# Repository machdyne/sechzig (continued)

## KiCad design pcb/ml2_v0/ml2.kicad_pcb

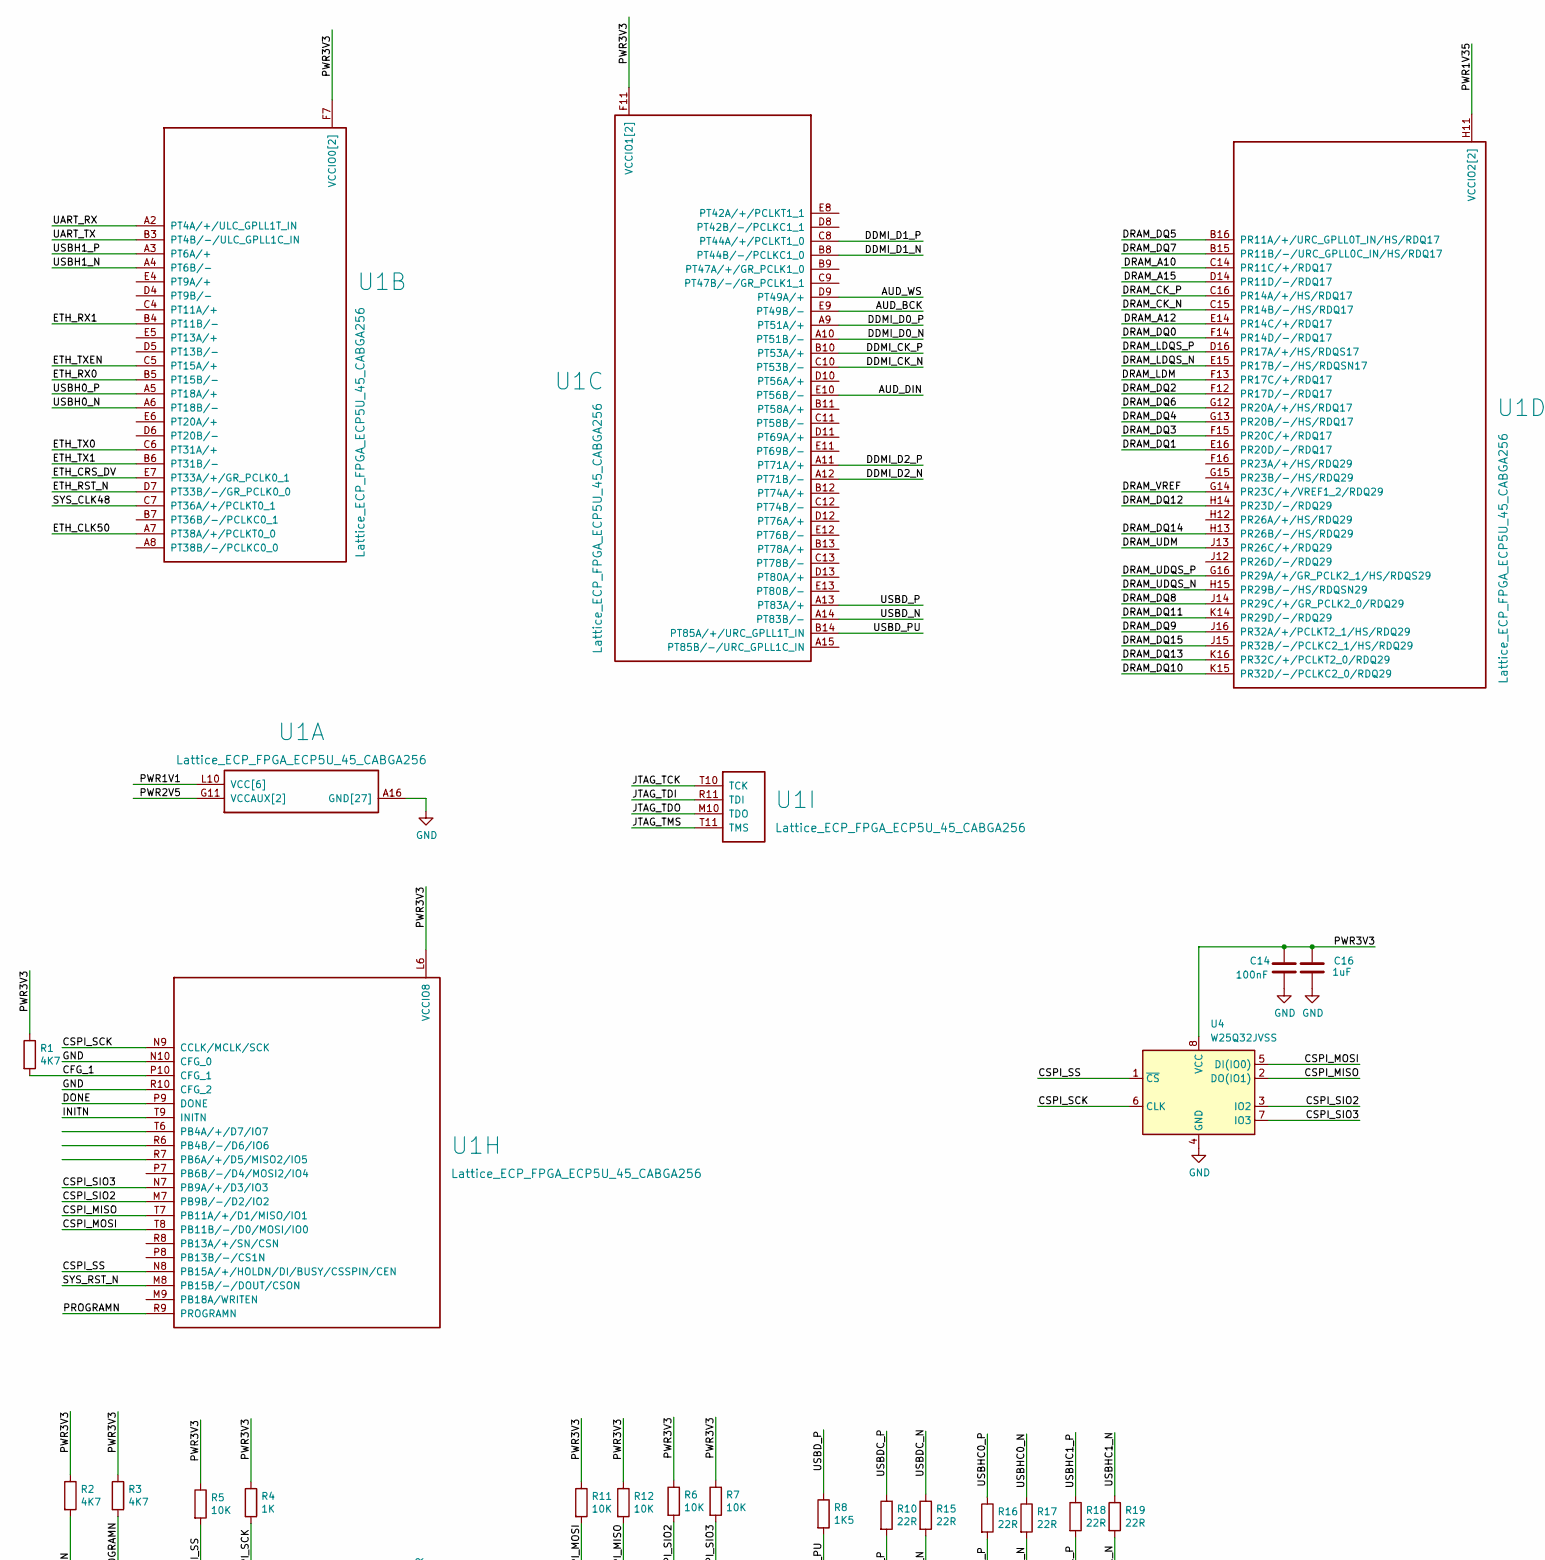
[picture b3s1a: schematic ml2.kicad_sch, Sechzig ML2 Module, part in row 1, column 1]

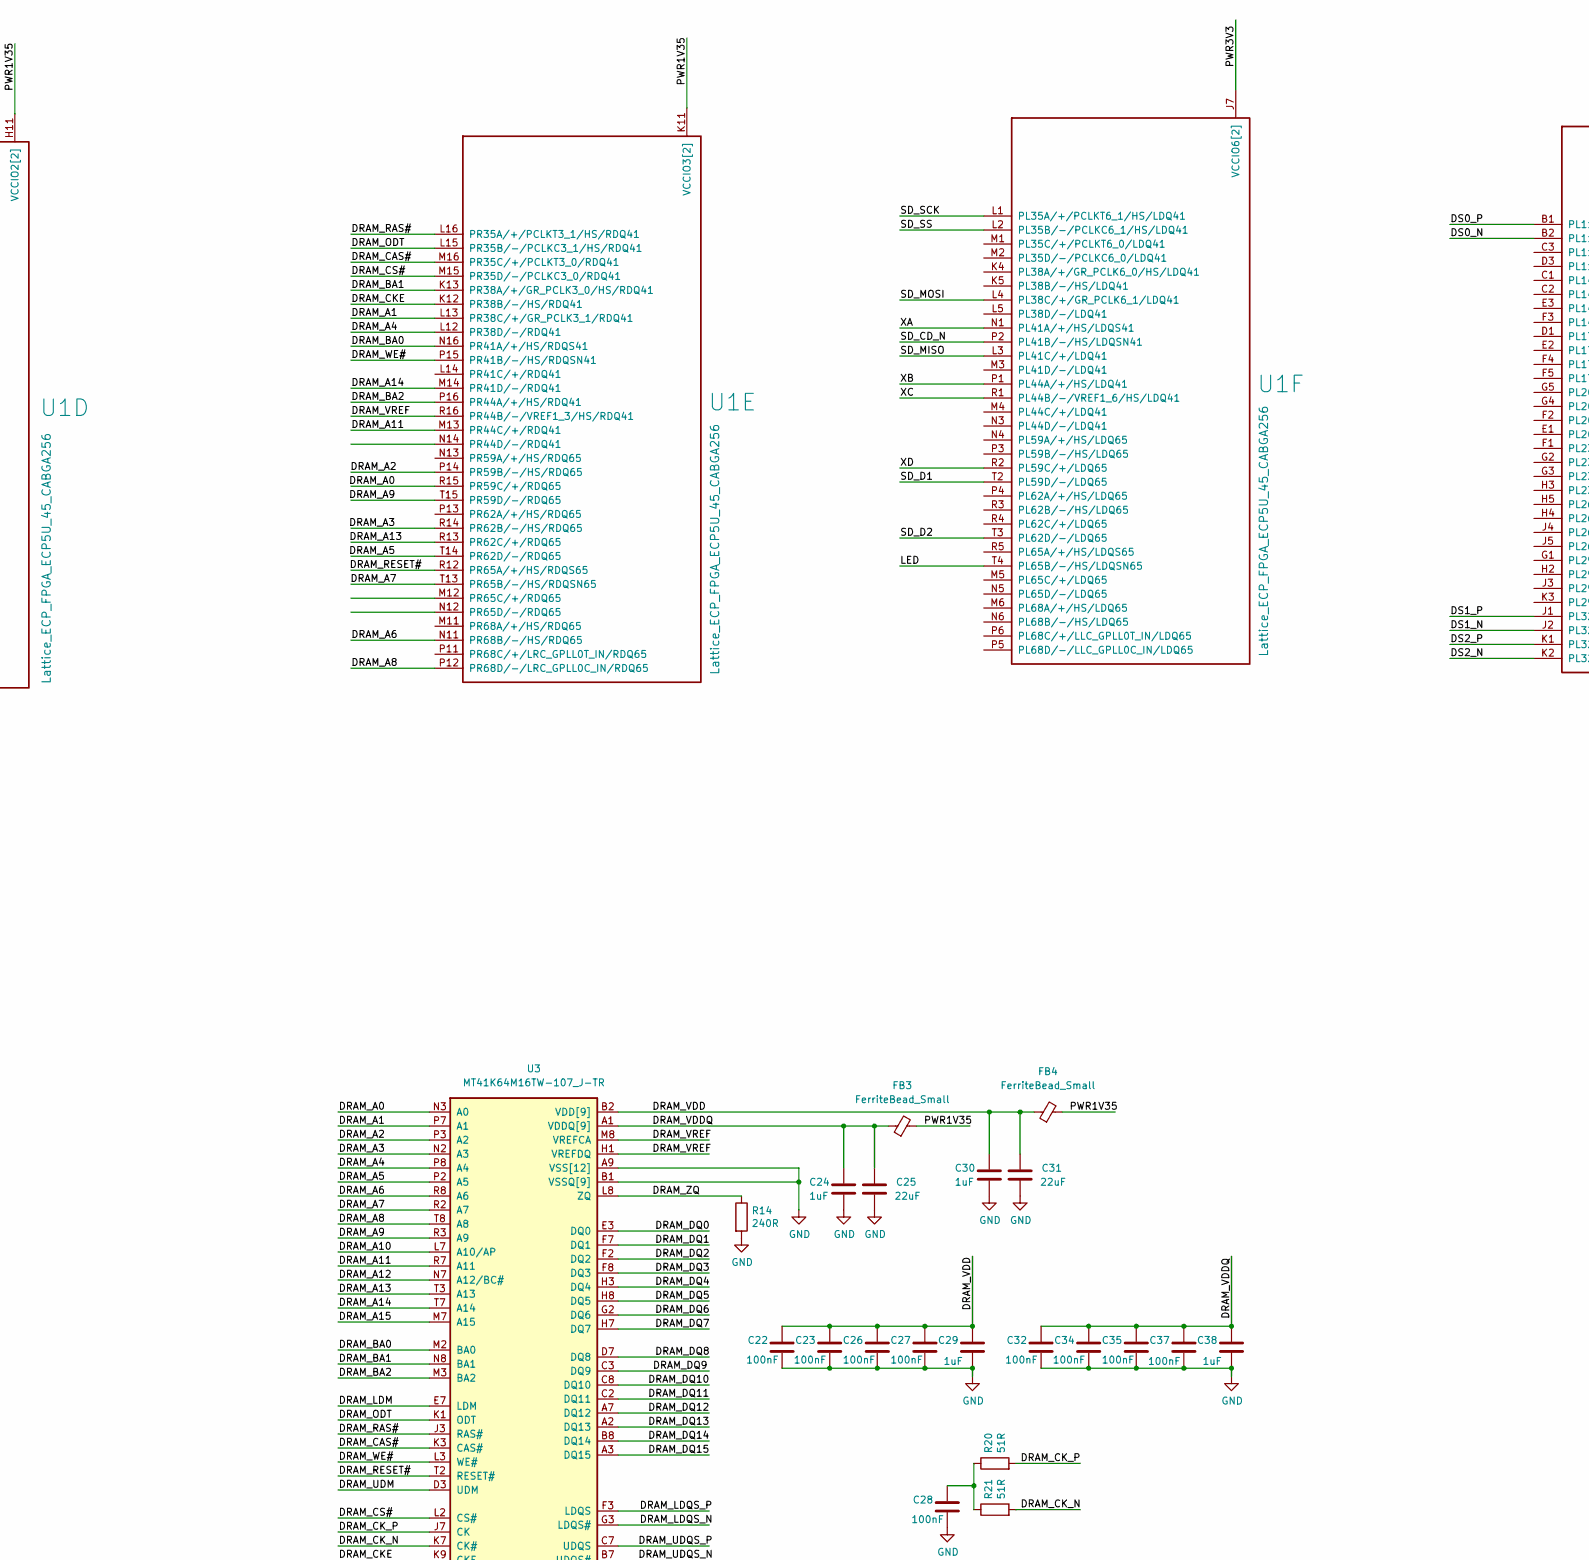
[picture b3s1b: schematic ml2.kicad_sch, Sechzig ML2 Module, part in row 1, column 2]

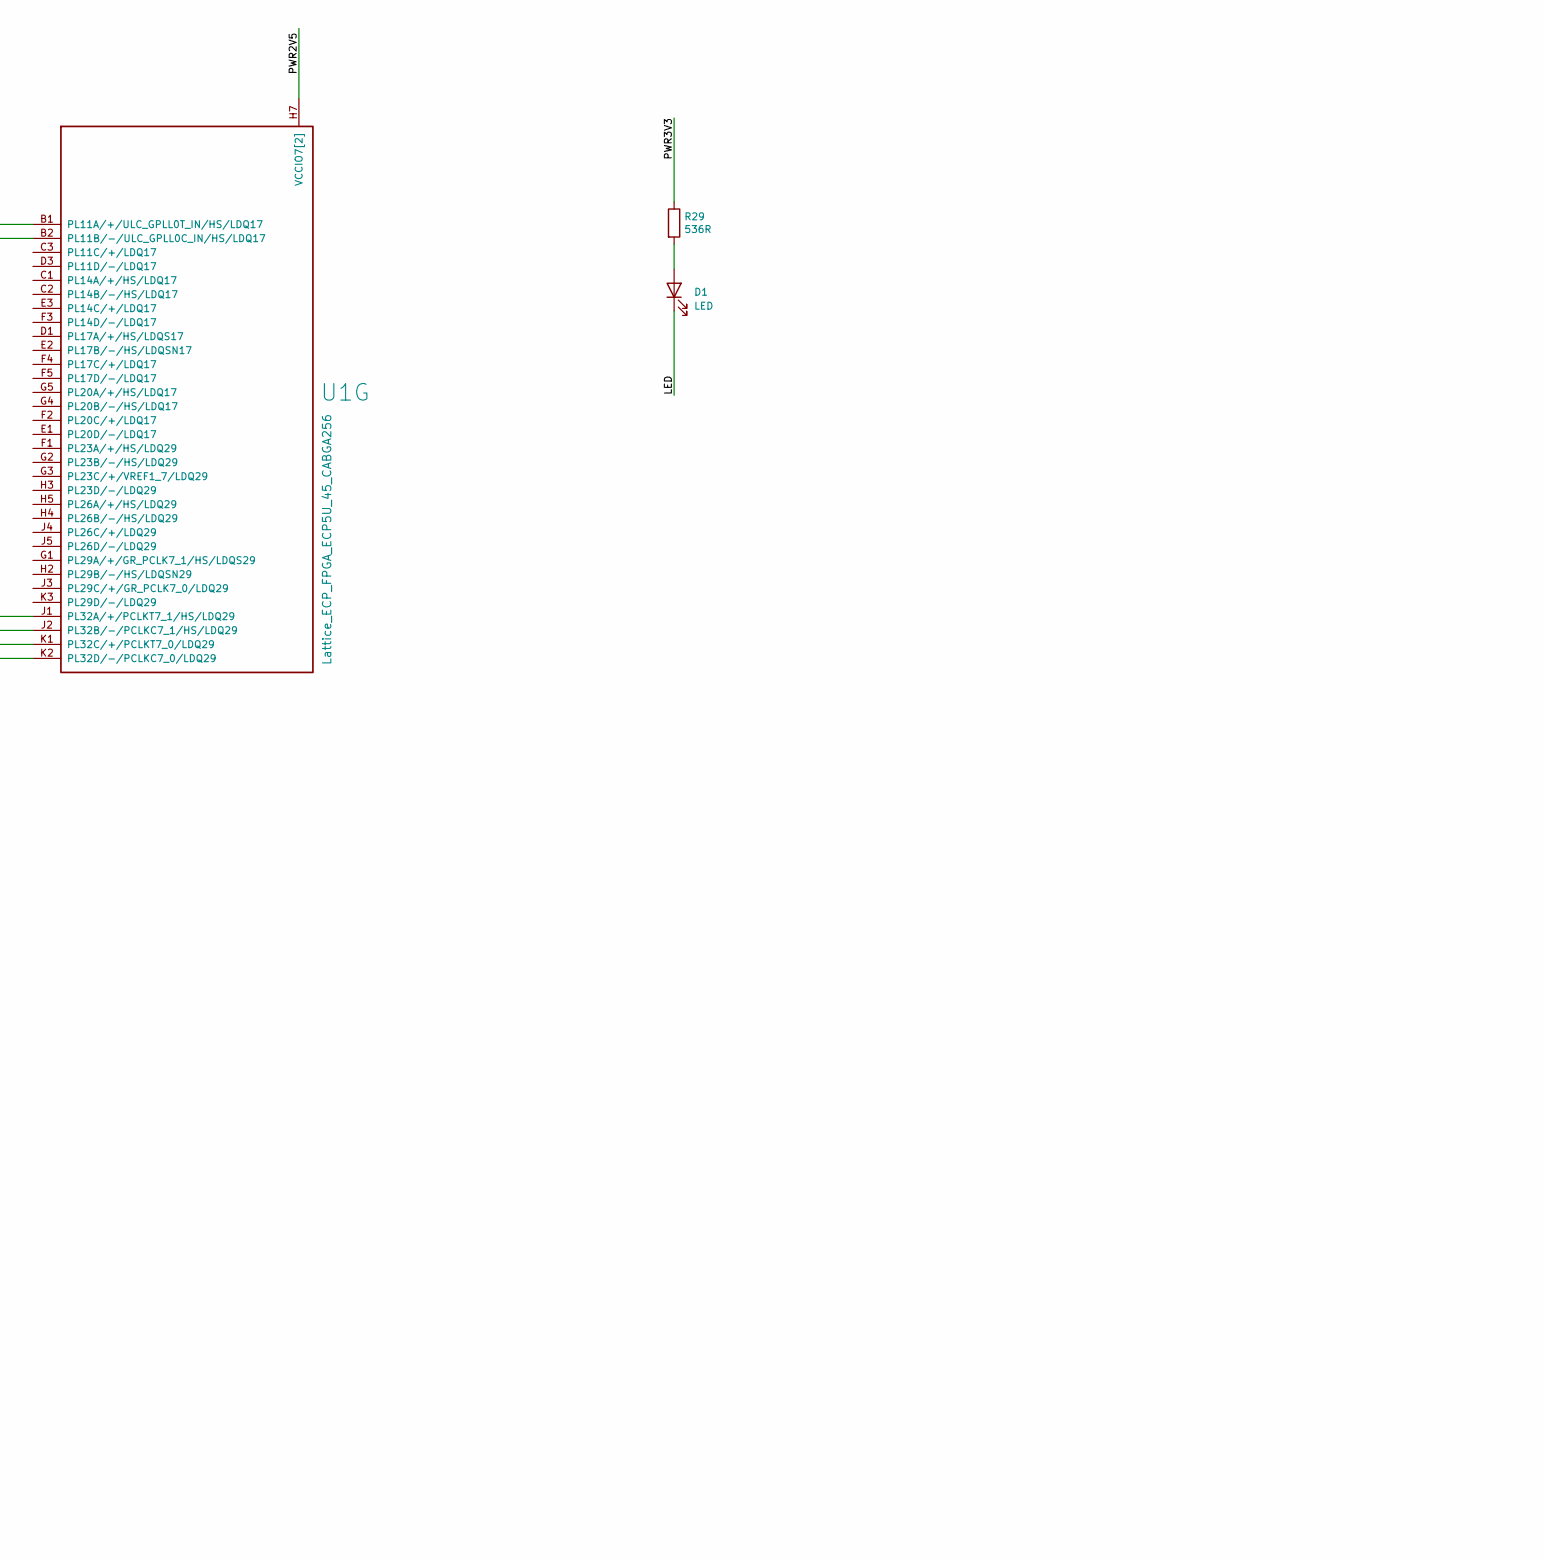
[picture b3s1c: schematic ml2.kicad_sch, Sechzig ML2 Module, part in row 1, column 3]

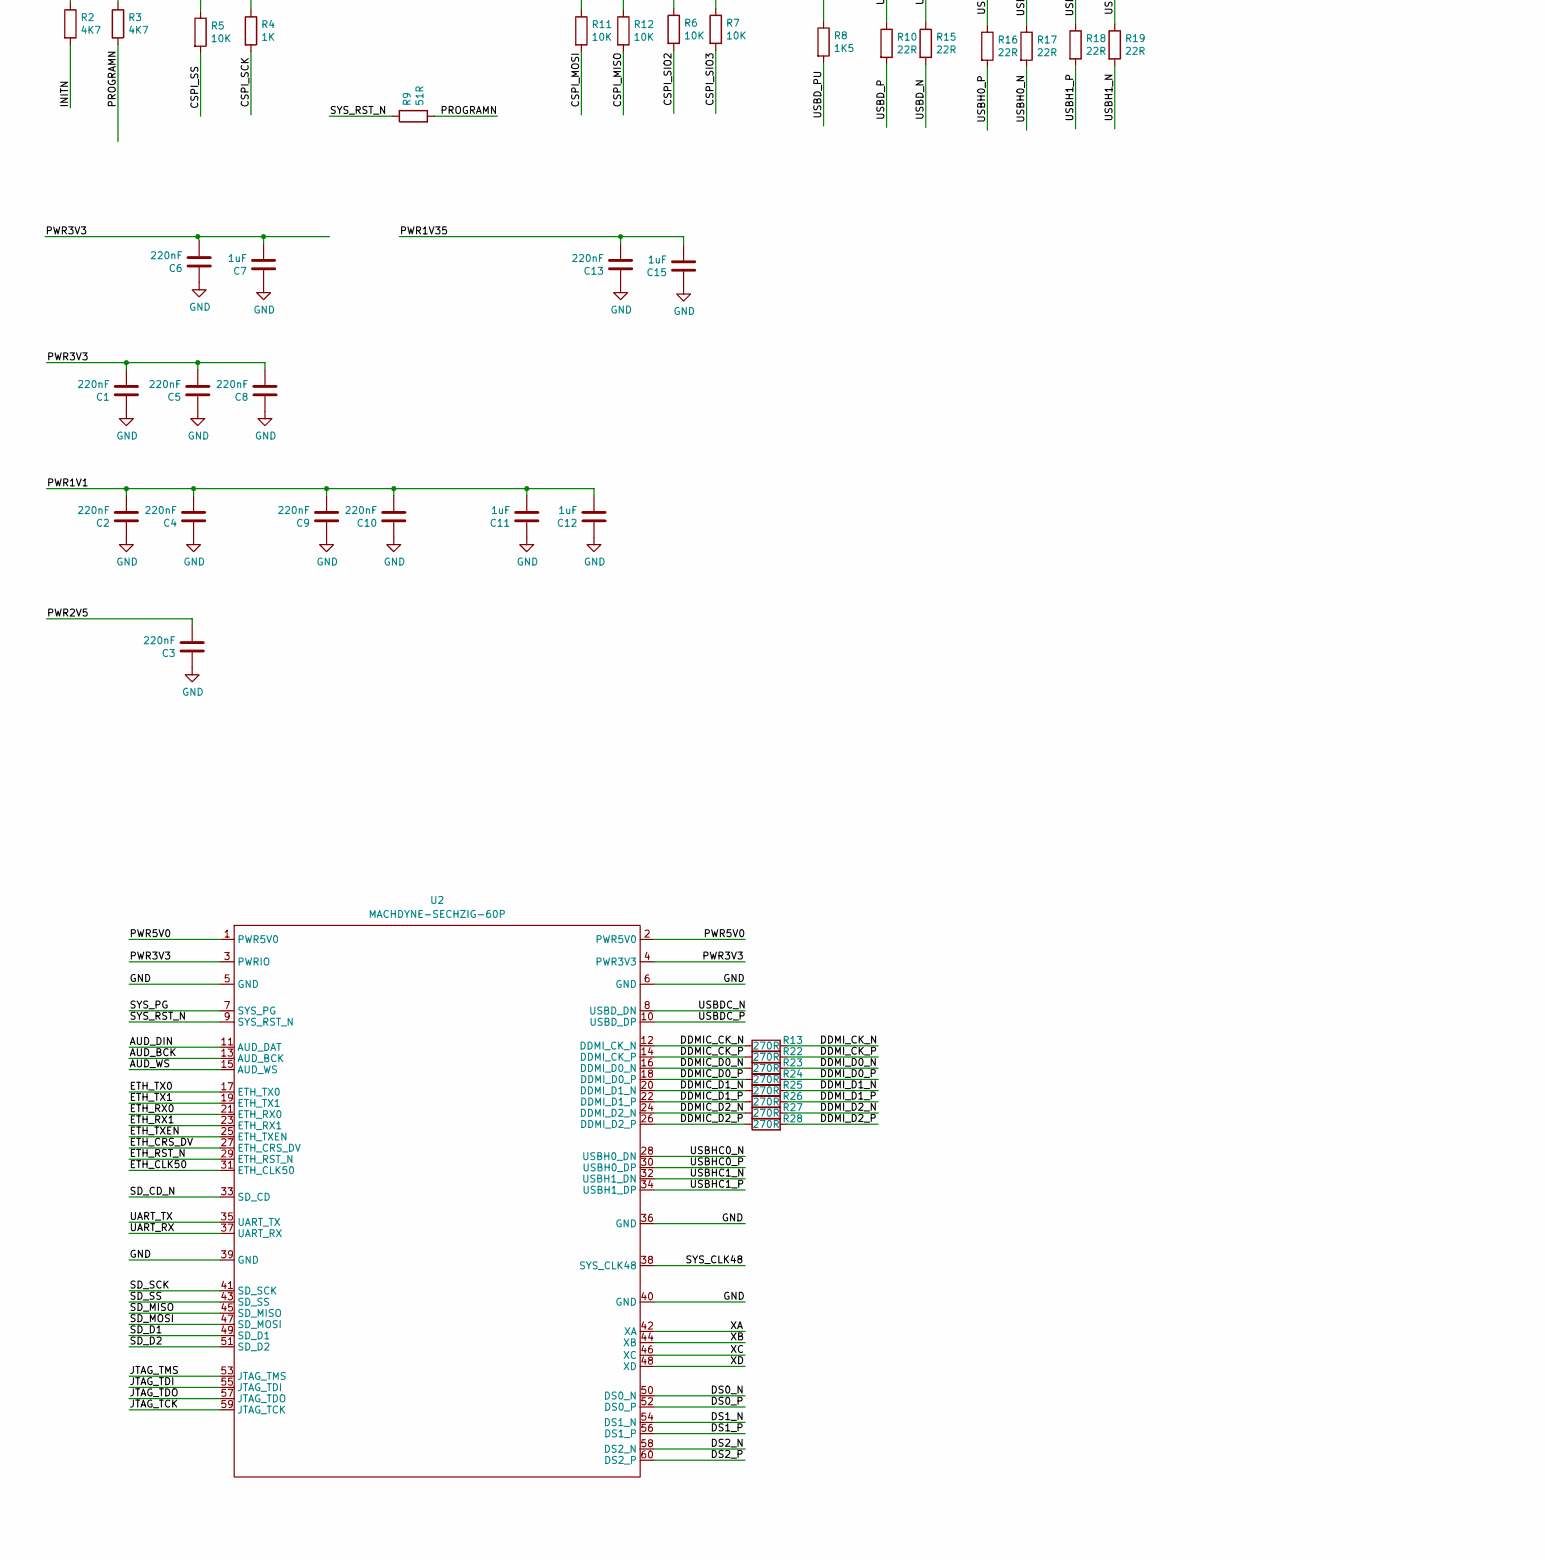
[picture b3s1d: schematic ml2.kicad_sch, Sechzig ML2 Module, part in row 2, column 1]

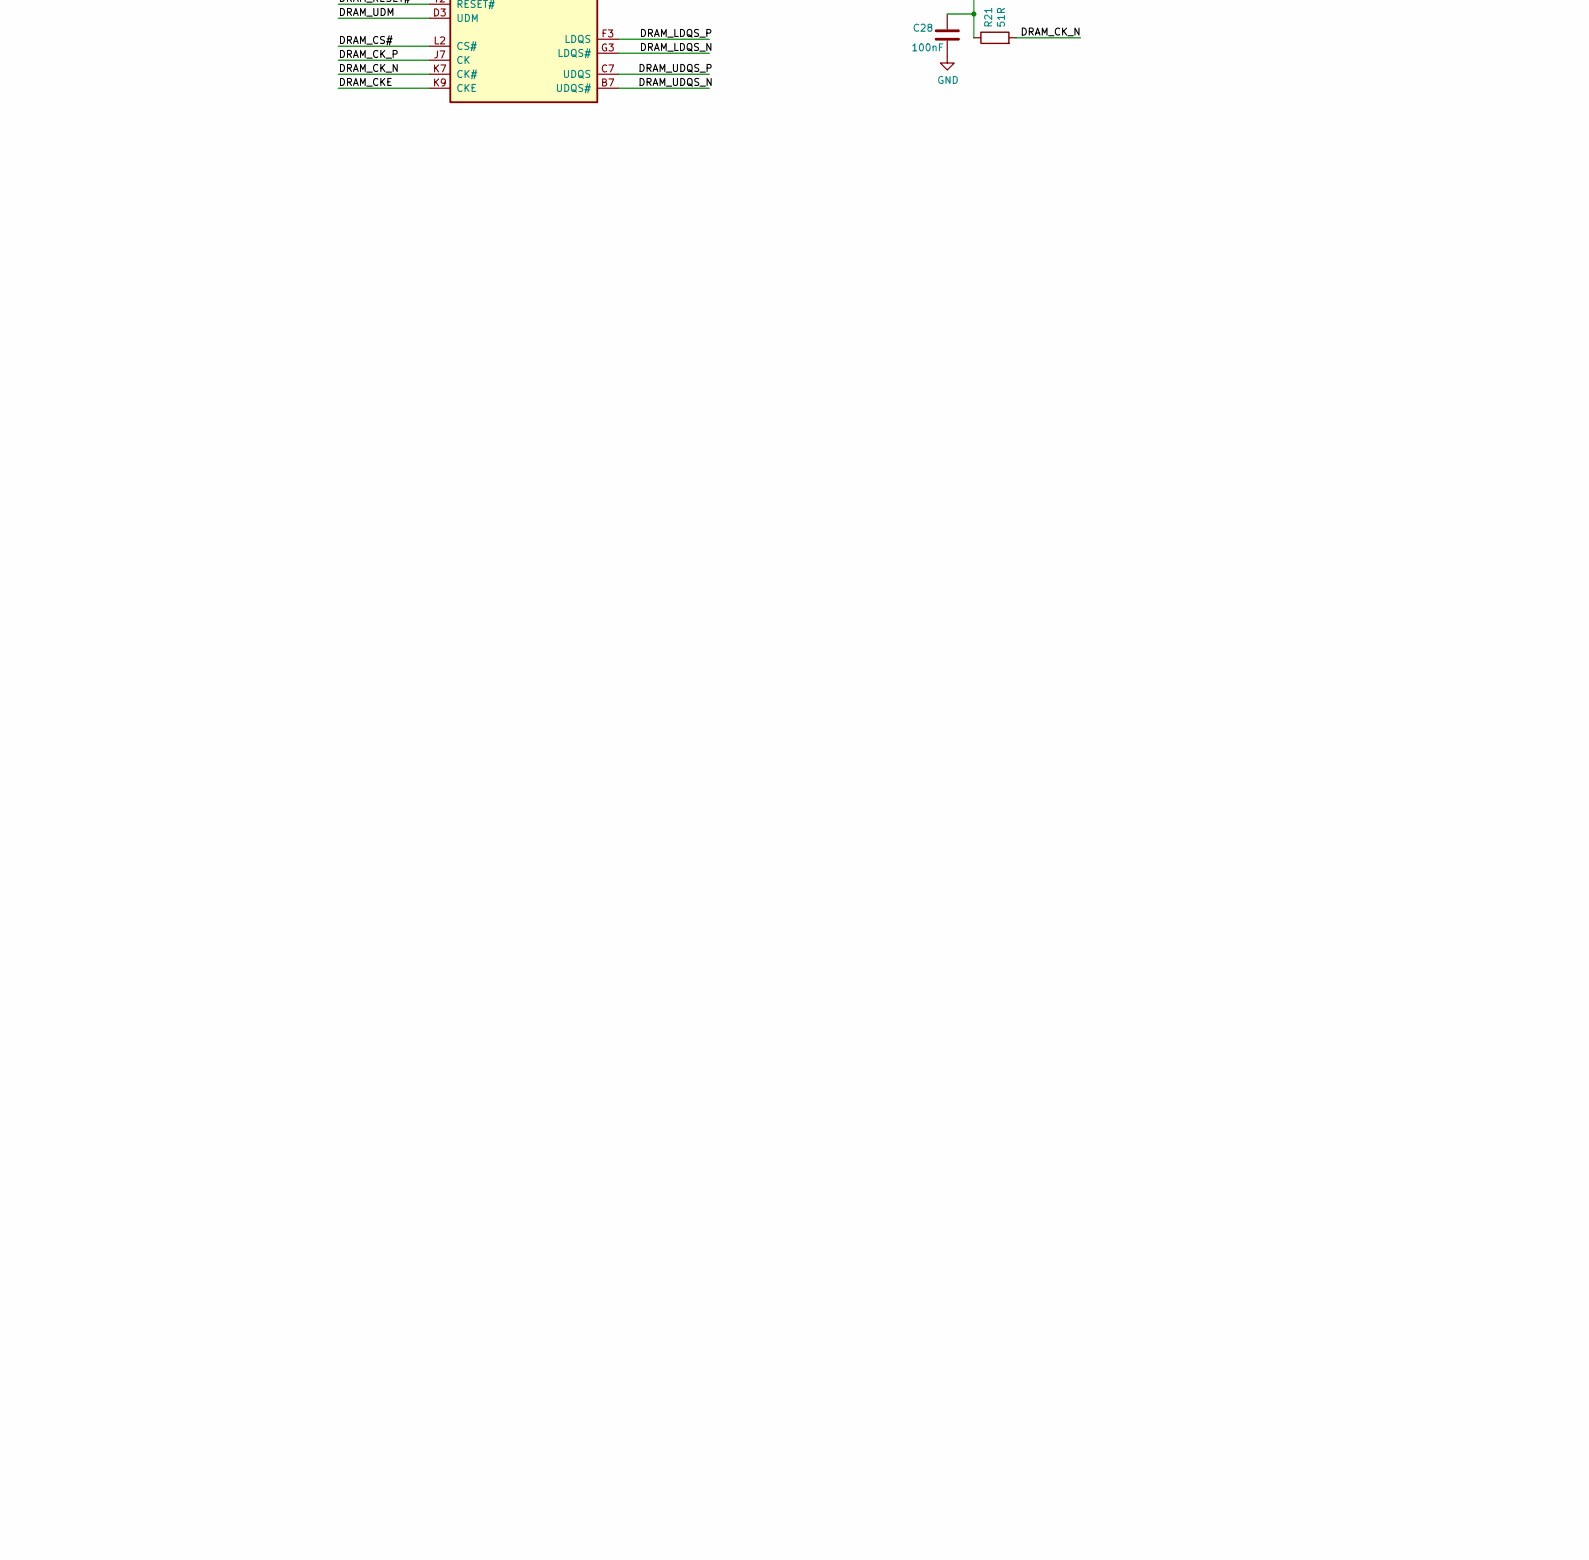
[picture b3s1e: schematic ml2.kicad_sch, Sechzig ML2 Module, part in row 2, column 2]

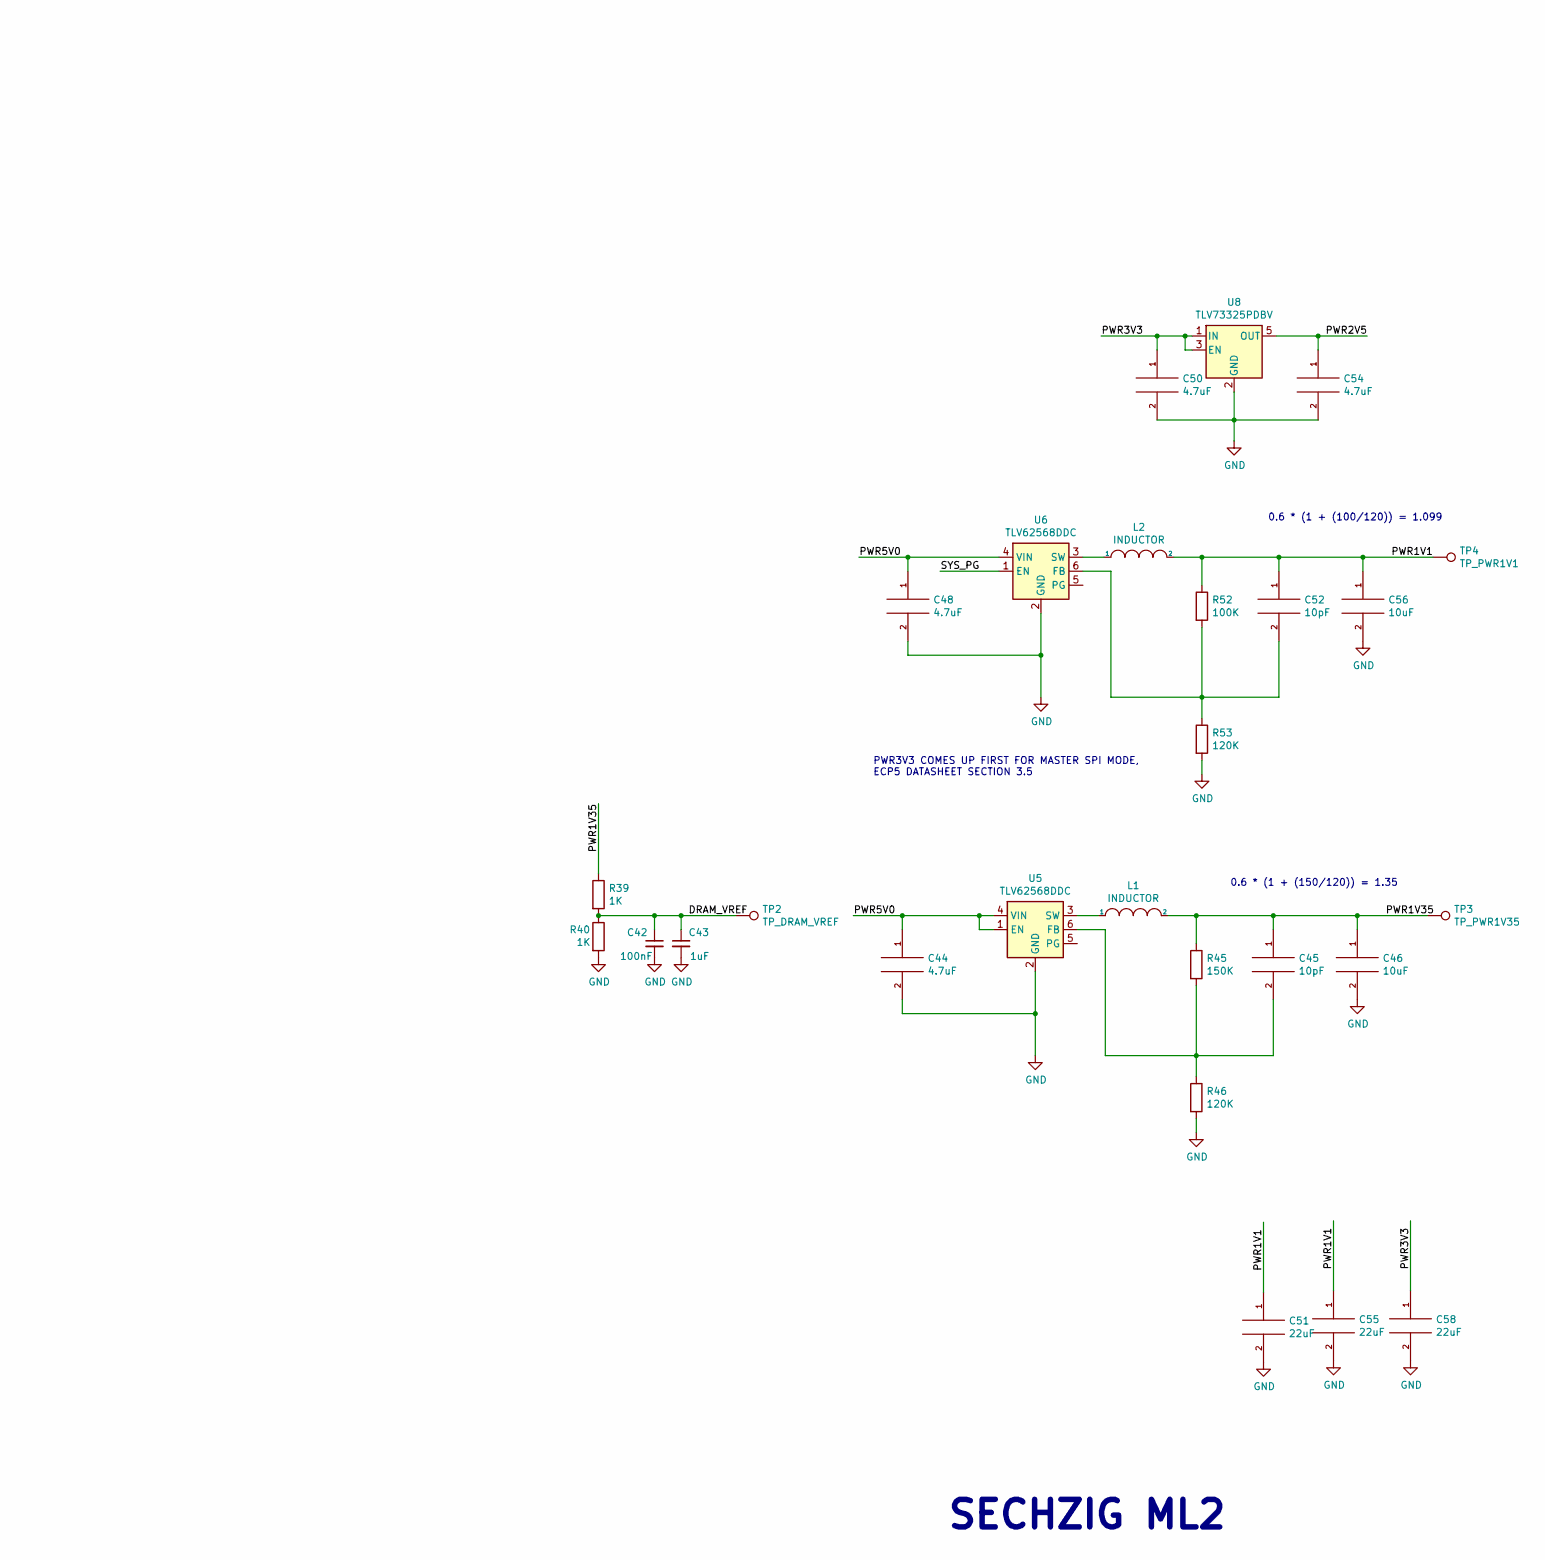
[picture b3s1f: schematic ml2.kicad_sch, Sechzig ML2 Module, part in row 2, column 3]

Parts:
C1, C2, C3, C4, C5, C6, C8, C9, C10, C13: 220nF; C_0603_1608Metric
C7, C11, C12, C15, C16, C43: 1uF; C_0603_1608Metric
C14, C42: 100nF; C_0603_1608Metric
C22, C23, C26, C27, C32, C34, C35, C37: 100nF; C_0402_1005Metric
C24, C29, C30, C38: 1uF; C_0402_1005Metric
C25, C31: 22uF; R_0603_1608Metric
C28: 100nF; R_0603_1608Metric
C44, C48, C50, C54: 4.7uF; C_0603_1608Metric
C45, C52: 10pF; C_0603_1608Metric
C46, C56: 10uF; C_0603_1608Metric
C51, C55, C58: 22uF; C_0603_1608Metric
D1: LED; LED_0603_1608Metric
FB3, FB4: FerriteBead_Small; R_0603_1608Metric
L1, L2: INDUCTOR; L_0805_2012Metric
R1, R2, R3: 4K7; R_0603_1608Metric
R4, R39, R40: 1K; R_0603_1608Metric
R5, R6, R7, R11, R12: 10K; R_0603_1608Metric
R8: 1K5; R_0402_1005Metric
R9, R20, R21: 51R; R_0603_1608Metric
R10, R15, R16, R17, R18, R19: 22R; R_0402_1005Metric
R13, R22, R23, R24, R25, R26, R27, R28: 270R; R_0402_1005Metric
R14: 240R; R_0603_1608Metric
R29: 536R; R_0603_1608Metric
R45: 150K; R_0603_1608Metric
R46, R53: 120K; R_0603_1608Metric
R52: 100K; R_0603_1608Metric
TP2: TP_DRAM_VREF; TestPoint_THTPad_D1.0mm_Drill0.5mm
TP3: TP_PWR1V35; TestPoint_THTPad_D1.0mm_Drill0.5mm
TP4: TP_PWR1V1; TestPoint_THTPad_D1.0mm_Drill0.5mm
U1: Lattice_ECP_FPGA_ECP5U_45_CABGA256; BGA-256_14.0x14.0mm_Layout16x16_P0.8mm_Ball0.45mm_Pad0.32mm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
U2: MACHDYNE-SECHZIG-60P; MACHDYNE_EDGE_60P
U3: MT41K64M16TW-107_J-TR; BGA-96_9.0x13.0mm_Layout2x3x16_P0.8mm_FIXED_SILK
U4: W25Q32JVSS; SOIC-8_3.9x4.9mm_P1.27mm
U5, U6: TLV62568DDC; SOT-23-6
U8: TLV73325PDBV; SOT-23-5

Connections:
/AUD_BCK: U1.E9 (PT49B/-), U2.13 (AUD_BCK)
/AUD_DIN: U1.E10 (PT56B/-), U2.11 (AUD_DAT)
/AUD_WS: U1.D9 (PT49A/+), U2.15 (AUD_WS)
/CFG_1: R1.2, U1.P10 (CFG_1)
/CSPI_MISO: R12.2, U1.T7 (PB11A/+/D1/MISO/IO1), U4.2 (DO(IO1))
/CSPI_MOSI: R11.2, U1.T8 (PB11B/-/D0/MOSI/IO0), U4.5 (DI(IO0))
/CSPI_SCK: R4.2, U1.N9 (CCLK/MCLK/SCK), U4.6 (CLK)
/CSPI_SIO2: R6.2, U1.M7 (PB9B/-/D2/IO2), U4.3 (IO2)
/CSPI_SIO3: R7.2, U1.N7 (PB9A/+/D3/IO3), U4.7 (IO3)
/CSPI_SS: R5.2, U1.N8 (PB15A/+/HOLDN/DI/BUSY/CSSPIN/CEN), U4.1 (~CS)
/DDMIC_CK_N: R13.1, U2.12 (DDMI_CK_N)
/DDMIC_CK_P: R22.1, U2.14 (DDMI_CK_P)
/DDMIC_D0_N: R23.1, U2.16 (DDMI_D0_N)
/DDMIC_D0_P: R24.1, U2.18 (DDMI_D0_P)
/DDMIC_D1_N: R25.1, U2.20 (DDMI_D1_N)
/DDMIC_D1_P: R26.1, U2.22 (DDMI_D1_P)
/DDMIC_D2_N: R27.1, U2.24 (DDMI_D2_N)
/DDMIC_D2_P: R28.1, U2.26 (DDMI_D2_P)
/DDMI_CK_N: R13.2, U1.C10 (PT53B/-)
/DDMI_CK_P: R22.2, U1.B10 (PT53A/+)
/DDMI_D0_N: R23.2, U1.A10 (PT51B/-)
/DDMI_D0_P: R24.2, U1.A9 (PT51A/+)
/DDMI_D1_N: R25.2, U1.B8 (PT44B/-/PCLKC1_0)
/DDMI_D1_P: R26.2, U1.C8 (PT44A/+/PCLKT1_0)
/DDMI_D2_N: R27.2, U1.A12 (PT71B/-)
/DDMI_D2_P: R28.2, U1.A11 (PT71A/+)
/DONE: U1.P9 (DONE)
/DRAM_A0: U1.R15 (PR59C/+/RDQ65), U3.N3 (A0)
/DRAM_A1: U1.L13 (PR38C/+/GR_PCLK3_1/RDQ41), U3.P7 (A1)
/DRAM_A2: U1.P14 (PR59B/-/HS/RDQ65), U3.P3 (A2)
/DRAM_A3: U1.R14 (PR62B/-/HS/RDQ65), U3.N2 (A3)
/DRAM_A4: U1.L12 (PR38D/-/RDQ41), U3.P8 (A4)
/DRAM_A5: U1.T14 (PR62D/-/RDQ65), U3.P2 (A5)
/DRAM_A6: U1.N11 (PR68B/-/HS/RDQ65), U3.R8 (A6)
/DRAM_A7: U1.T13 (PR65B/-/HS/RDQSN65), U3.R2 (A7)
/DRAM_A8: U1.P12 (PR68D/-/LRC_GPLL0C_IN/RDQ65), U3.T8 (A8)
/DRAM_A9: U1.T15 (PR59D/-/RDQ65), U3.R3 (A9)
/DRAM_A10: U1.C14 (PR11C/+/RDQ17), U3.L7 (A10/AP)
/DRAM_A11: U1.M13 (PR44C/+/RDQ41), U3.R7 (A11)
/DRAM_A12: U1.E14 (PR14C/+/RDQ17), U3.N7 (A12/BC#)
/DRAM_A13: U1.R13 (PR62C/+/RDQ65), U3.T3 (A13)
/DRAM_A14: U1.M14 (PR41D/-/RDQ41), U3.T7 (A14)
/DRAM_A15: U1.D14 (PR11D/-/RDQ17), U3.M7 (A15)
/DRAM_BA0: U1.N16 (PR41A/+/HS/RDQS41), U3.M2 (BA0)
/DRAM_BA1: U1.K13 (PR38A/+/GR_PCLK3_0/HS/RDQ41), U3.N8 (BA1)
/DRAM_BA2: U1.P16 (PR44A/+/HS/RDQ41), U3.M3 (BA2)
/DRAM_CAS#: U1.M16 (PR35C/+/PCLKT3_0/RDQ41), U3.K3 (CAS#)
/DRAM_CKE: U1.K12 (PR38B/-/HS/RDQ41), U3.K9 (CKE)
/DRAM_CK_N: R21.2, U1.C15 (PR14B/-/HS/RDQ17), U3.K7 (CK#)
/DRAM_CK_P: R20.2, U1.C16 (PR14A/+/HS/RDQ17), U3.J7 (CK)
/DRAM_CS#: U1.M15 (PR35D/-/PCLKC3_0/RDQ41), U3.L2 (CS#)
/DRAM_DQ0: U1.F14 (PR14D/-/RDQ17), U3.E3 (DQ0)
/DRAM_DQ1: U1.E16 (PR20D/-/RDQ17), U3.F7 (DQ1)
/DRAM_DQ2: U1.F12 (PR17D/-/RDQ17), U3.F2 (DQ2)
/DRAM_DQ3: U1.F15 (PR20C/+/RDQ17), U3.F8 (DQ3)
/DRAM_DQ4: U1.G13 (PR20B/-/HS/RDQ17), U3.H3 (DQ4)
/DRAM_DQ5: U1.B16 (PR11A/+/URC_GPLL0T_IN/HS/RDQ17), U3.H8 (DQ5)
/DRAM_DQ6: U1.G12 (PR20A/+/HS/RDQ17), U3.G2 (DQ6)
/DRAM_DQ7: U1.B15 (PR11B/-/URC_GPLL0C_IN/HS/RDQ17), U3.H7 (DQ7)
/DRAM_DQ8: U1.J14 (PR29C/+/GR_PCLK2_0/RDQ29), U3.D7 (DQ8)
/DRAM_DQ9: U1.J16 (PR32A/+/PCLKT2_1/HS/RDQ29), U3.C3 (DQ9)
/DRAM_DQ10: U1.K15 (PR32D/-/PCLKC2_0/RDQ29), U3.C8 (DQ10)
/DRAM_DQ11: U1.K14 (PR29D/-/RDQ29), U3.C2 (DQ11)
/DRAM_DQ12: U1.H14 (PR23D/-/RDQ29), U3.A7 (DQ12)
/DRAM_DQ13: U1.K16 (PR32C/+/PCLKT2_0/RDQ29), U3.A2 (DQ13)
/DRAM_DQ14: U1.H13 (PR26B/-/HS/RDQ29), U3.B8 (DQ14)
/DRAM_DQ15: U1.J15 (PR32B/-/PCLKC2_1/HS/RDQ29), U3.A3 (DQ15)
/DRAM_LDM: U1.F13 (PR17C/+/RDQ17), U3.E7 (LDM)
/DRAM_LDQS_N: U1.E15 (PR17B/-/HS/RDQSN17), U3.G3 (LDQS#)
/DRAM_LDQS_P: U1.D16 (PR17A/+/HS/RDQS17), U3.F3 (LDQS)
/DRAM_ODT: U1.L15 (PR35B/-/PCLKC3_1/HS/RDQ41), U3.K1 (ODT)
/DRAM_RAS#: U1.L16 (PR35A/+/PCLKT3_1/HS/RDQ41), U3.J3 (RAS#)
/DRAM_RESET#: U1.R12 (PR65A/+/HS/RDQS65), U3.T2 (RESET#)
/DRAM_UDM: U1.J13 (PR26C/+/RDQ29), U3.D3 (UDM)
/DRAM_UDQS_N: U1.H15 (PR29B/-/HS/RDQSN29), U3.B7 (UDQS#)
/DRAM_UDQS_P: U1.G16 (PR29A/+/GR_PCLK2_1/HS/RDQS29), U3.C7 (UDQS)
/DRAM_VDD: C22.1, C23.1, C26.1, C27.1, C29.1, C30.1, C31.1, FB4.1, U3.B2 (VDD[9]), U3.D9 (VDD), U3.G7 (VDD), U3.K2 (VDD), U3.K8 (VDD), U3.N1 (VDD), U3.N9 (VDD), U3.R1 (VDD), U3.R9 (VDD)
/DRAM_VDDQ: C24.1, C25.1, C32.1, C34.1, C35.1, C37.1, C38.1, FB3.1, U3.A1 (VDDQ[9]), U3.A8 (VDDQ), U3.C1 (VDDQ), U3.C9 (VDDQ), U3.D2 (VDDQ), U3.E9 (VDDQ), U3.F1 (VDDQ), U3.H2 (VDDQ), U3.H9 (VDDQ)
/DRAM_VREF: C42.1, C43.1, R39.2, R40.1, TP2.1, U1.G14 (PR23C/+/VREF1_2/RDQ29), U1.R16 (PR44B/-/VREF1_3/HS/RDQ41), U3.H1 (VREFDQ), U3.M8 (VREFCA)
/DRAM_WE#: U1.P15 (PR41B/-/HS/RDQSN41), U3.L3 (WE#)
/DRAM_ZQ: R14.1, U3.L8 (ZQ)
/DS0_N: U1.B2 (PL11B/-/ULC_GPLL0C_IN/HS/LDQ17), U2.50 (DS0_N)
/DS0_P: U1.B1 (PL11A/+/ULC_GPLL0T_IN/HS/LDQ17), U2.52 (DS0_P)
/DS1_N: U1.J2 (PL32B/-/PCLKC7_1/HS/LDQ29), U2.54 (DS1_N)
/DS1_P: U1.J1 (PL32A/+/PCLKT7_1/HS/LDQ29), U2.56 (DS1_P)
/DS2_N: U1.K2 (PL32D/-/PCLKC7_0/LDQ29), U2.58 (DS2_N)
/DS2_P: U1.K1 (PL32C/+/PCLKT7_0/LDQ29), U2.60 (DS2_P)
/ETH_CLK50: U1.A7 (PT38A/+/PCLKT0_0), U2.31 (ETH_CLK50)
/ETH_CRS_DV: U1.E7 (PT33A/+/GR_PCLK0_1), U2.27 (ETH_CRS_DV)
/ETH_RST_N: U1.D7 (PT33B/-/GR_PCLK0_0), U2.29 (ETH_RST_N)
/ETH_RX0: U1.B5 (PT15B/-), U2.21 (ETH_RX0)
/ETH_RX1: U1.B4 (PT11B/-), U2.23 (ETH_RX1)
/ETH_TX0: U1.C6 (PT31A/+), U2.17 (ETH_TX0)
/ETH_TX1: U1.B6 (PT31B/-), U2.19 (ETH_TX1)
/ETH_TXEN: U1.C5 (PT15A/+), U2.25 (ETH_TXEN)
/INITN: R2.2, U1.T9 (INITN)
/JTAG_TCK: U1.T10 (TCK), U2.59 (JTAG_TCK); also elsewhere on the board
/JTAG_TDI: U1.R11 (TDI), U2.55 (JTAG_TDI); also elsewhere on the board
/JTAG_TDO: U1.M10 (TDO), U2.57 (JTAG_TDO); also elsewhere on the board
/JTAG_TMS: U1.T11 (TMS), U2.53 (JTAG_TMS); also elsewhere on the board
/LED: D1.1 (K), U1.T4 (PL65B/-/HS/LDQSN65)
/PROGRAMN: R3.2, R9.2, U1.R9 (PROGRAMN)
/PWR1V1: C2.2, C4.2, C9.2, C10.2, C11.2, C12.2, C51.1, C52.1, C55.1, C56.1, L2.2, R52.1, TP4.1, U1.G6 (VCC[6]), U1.G7 (VCC[6]), U1.G9 (VCC[6]), U1.L8 (VCC[6]), U1.L9 (VCC[6]), U1.L10 (VCC[6])
/PWR1V35: C13.2, C15.2, C45.1, C46.1, FB3.2, FB4.2, L1.2, R39.1, R45.1, TP3.1, U1.H11 (VCCIO2[2]), U1.J11 (VCCIO2[2]), U1.K11 (VCCIO3[2]), U1.L11 (VCCIO3[2])
/PWR2V5: C3.2, C54.1, U1.G11 (VCCAUX[2]), U1.H6 (VCCIO7[2]), U1.H7 (VCCIO7[2]), U1.L7 (VCCAUX[2]), U8.5 (OUT)
/PWR3V3: C1.2, C5.2, C6.2, C7.2, C8.2, C14.1, C16.1, C50.1, C58.1, R1.1, R2.1, R3.1, R4.1, R5.1, R6.1, R7.1, R11.1, R12.1, R29.1, U1.F6 (VCCIO0[2]), U1.F7 (VCCIO0[2]), U1.F10 (VCCIO1[2]), U1.F11 (VCCIO1[2]), U1.J6 (VCCIO6[2]), U1.J7 (VCCIO6[2]), U1.L6 (VCCIO8), U2.3 (PWRIO), U2.4 (PWR3V3), U4.8 (VCC), U8.1 (IN), U8.3 (EN); also elsewhere on the board
/PWR5V0: C44.1, C48.1, U2.1 (PWR5V0), U2.2 (PWR5V0), U5.1 (EN), U5.4 (VIN), U6.4 (VIN)
/SD_CD_N: U1.P2 (PL41B/-/HS/LDQSN41), U2.33 (SD_CD)
/SD_D1: U1.T2 (PL59D/-/LDQ65), U2.49 (SD_D1)
/SD_D2: U1.T3 (PL62D/-/LDQ65), U2.51 (SD_D2)
/SD_MISO: U1.L3 (PL41C/+/LDQ41), U2.45 (SD_MISO)
/SD_MOSI: U1.L4 (PL38C/+/GR_PCLK6_1/LDQ41), U2.47 (SD_MOSI)
/SD_SCK: U1.L1 (PL35A/+/PCLKT6_1/HS/LDQ41), U2.41 (SD_SCK)
/SD_SS: U1.L2 (PL35B/-/PCLKC6_1/HS/LDQ41), U2.43 (SD_SS)
/SYS_CLK48: U1.C7 (PT36A/+/PCLKT0_1), U2.38 (SYS_CLK48)
/SYS_PG: U2.7 (SYS_PG), U6.1 (EN)
/SYS_RST_N: R9.1, U1.M8 (PB15B/-/DOUT/CSON), U2.9 (SYS_RST_N)
/UART_RX: U1.A2 (PT4A/+/ULC_GPLL1T_IN), U2.37 (UART_RX)
/UART_TX: U1.B3 (PT4B/-/ULC_GPLL1C_IN), U2.35 (UART_TX)
/USBDC_N: R15.1, U2.8 (USBD_DN)
/USBDC_P: R10.1, U2.10 (USBD_DP)
/USBD_N: R15.2, U1.A14 (PT83B/-)
/USBD_P: R8.1, R10.2, U1.A13 (PT83A/+)
/USBD_PU: R8.2, U1.B14 (PT85A/+/URC_GPLL1T_IN)
/USBH0_N: R17.2, U1.A6 (PT18B/-)
/USBH0_P: R16.2, U1.A5 (PT18A/+)
/USBH1_N: R19.2, U1.A4 (PT6B/-)
/USBH1_P: R18.2, U1.A3 (PT6A/+)
/USBHC0_N: R17.1, U2.28 (USBH0_DN)
/USBHC0_P: R16.1, U2.30 (USBH0_DP)
/USBHC1_N: R19.1, U2.32 (USBH1_DN)
/USBHC1_P: R18.1, U2.34 (USBH1_DP)
/XA: U1.N1 (PL41A/+/HS/LDQS41), U2.42 (XA)
/XB: U1.P1 (PL44A/+/HS/LDQ41), U2.44 (XB)
/XC: U1.R1 (PL44B/-/VREF1_6/HS/LDQ41), U2.46 (XC)
/XD: U1.R2 (PL59C/+/LDQ65), U2.48 (XD)
GND: C1.1, C2.1, C3.1, C4.1, C5.1, C6.1, C7.1, C8.1, C9.1, C10.1, C11.1, C12.1, C13.1, C14.2, C15.1, C16.2, C22.2, C23.2, C24.2, C25.2, C26.2, C27.2, C28.2, C29.2, C30.2, C31.2, C32.2, C34.2, C35.2, C37.2, C38.2, C42.2, C43.2, C44.2, C46.2, C48.2, C50.2, C51.2, C54.2, C55.2, C56.2, C58.2, R14.2, R40.2, R46.2, R53.2, U1.A1 (GND[27]), U1.A16 (GND[27]), U1.D2 (GND[27]), U1.D15 (GND[27]), U1.F8 (GND[27]), U1.F9 (GND[27]), U1.G8 (GND[27]), U1.G10 (GND[27]), U1.H1 (GND[27]), U1.H8 (GND[27]), U1.H9 (GND[27]), U1.H10 (GND[27]), U1.H16 (GND[27]), U1.J8 (GND[27]), U1.J9 (GND[27]), U1.J10 (GND[27]), U1.K6 (GND[27]), U1.K7 (GND[27]), U1.K8 (GND[27]), U1.K9 (GND[27]), U1.K10 (GND[27]), U1.N2 (GND[27]), U1.N10 (CFG_0), U1.N15 (GND[27]), U1.R10 (CFG_2), U1.T1 (GND[27]), U1.T5 (GND[27]), U1.T12 (GND[27]), U1.T16 (GND[27]), U2.5 (GND), U2.6 (GND), U2.36 (GND), U2.39 (GND), U2.40 (GND), U3.A9 (VSS[12]), U3.B1 (VSSQ[9]), U3.B3 (VSS), U3.B9 (VSSQ), U3.D1 (VSSQ), U3.D8 (VSSQ), U3.E1 (VSS), U3.E2 (VSSQ), U3.E8 (VSSQ), U3.F9 (VSSQ), U3.G1 (VSSQ), U3.G9 (VSSQ), U3.J2 (VSS), U3.J8 (VSS), U3.M1 (VSS), U3.M9 (VSS), U3.P1 (VSS), U3.P9 (VSS), U3.T1 (VSS), U3.T9 (VSS), U4.4 (GND), U5.2 (GND), U6.2 (GND), U8.2 (GND); also elsewhere on the board
unnamed: C28.1, R20.1, R21.1
unnamed: C45.2, R45.2, R46.1, U5.6 (FB)
unnamed: C52.2, R52.2, R53.1, U6.6 (FB)
unnamed: D1.2 (A), R29.2
unnamed: L1.1, U5.3 (SW)
unnamed: L2.1, U6.3 (SW)

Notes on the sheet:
SECHZIG ML2
PWR3V3 COMES UP FIRST FOR MASTER SPI MODE, ECP5 DATASHEET SECTION 3.5
0.6 * (1 + (100/120)) = 1.099
0.6 * (1 + (150/120)) = 1.35

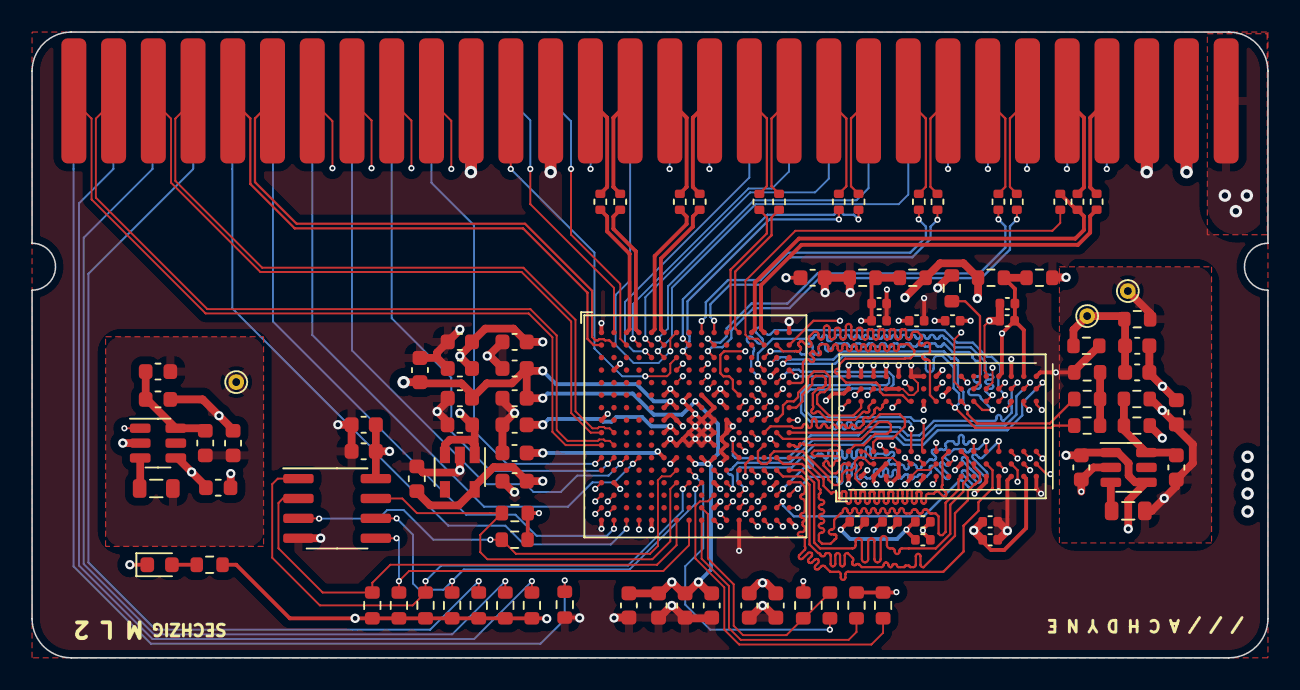
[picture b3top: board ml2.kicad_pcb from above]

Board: 6 copper layers, 79.0 x 40.0 mm, 98 parts (1 on the bottom side), 142 nets.

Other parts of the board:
R38, R42, R43, R44: 4K7; R_0603_1608Metric

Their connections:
/JTAG_TCK: R44.1; also elsewhere on the board
/JTAG_TDI: R38.2; also elsewhere on the board
/JTAG_TDO: R42.2; also elsewhere on the board
/JTAG_TMS: R43.2; also elsewhere on the board
/PWR3V3: R38.1, R42.1, R43.1; also elsewhere on the board
GND: R44.2; also elsewhere on the board

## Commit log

2023-06-23 update for v1 boards
2023-10-25 update pinout
2023-10-25 update kicad symbol
2023-10-25 update dimensions
2023-10-26 update signals
2023-11-14 add sechzig ml1 schematics and pcb layout
2023-11-14 add image
2023-12-04 add preliminary cart design
2023-12-17 update case
2024-02-15 add ml2 pcb
2024-03-06 add mx1 pcb
2024-03-07 add ml1.2 pcb
2024-03-19 update license
2024-07-25 add mx2
2024-09-29 add 3d-printable tray for holding modules
